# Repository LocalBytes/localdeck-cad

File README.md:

# LocalDeck CAD

## About

This is the repo for the LocalDeck CAD; it is split into multiple parts:

- [freecad](./freecad)
    - Uses FreeCAD v1
    - Contains all of the mechanical CAD resources
    - You should start with [asm-localdeck](./freecad/asm-localdeck.FCStd)
- [kicad](./kicad)
    - Uses Kicad v8
    - Contains all of the electrical CAD resources

## Contributing

The best way to contribute to the LocalDeck (and it's configurator) is by using the development version in your HomeAssistant, and reporting any issues you find.
Additionally, we would appreciate it if you were to be active on the Forum should we solicit feedback on a new feature or change.

We do not recommend pull-requests to this repo. Git doesn't handle CAD files too well.
If you are a mechanical or electrical engineer, the best way to contribute would be by opening 
If you are a developer, you can also contribute by submitting a pull request to this repository. Please be aware that any code contributed will become the property of Allport-IT LTD.

## Licence
This project is currently published with no specific licence:
- This program is distributed in the hope that it will be useful,
  but WITHOUT ANY WARRANTY
- As an individual user, you are free learn from it, and use it in your own projects
- You must not claim it as your own

Unless otherwise stated, all code is &copy; Allport-IT LTD. All rights reserved.  
"LocalBytes" and the LocalBytes Logo are &reg; of Allport-IT LTD.

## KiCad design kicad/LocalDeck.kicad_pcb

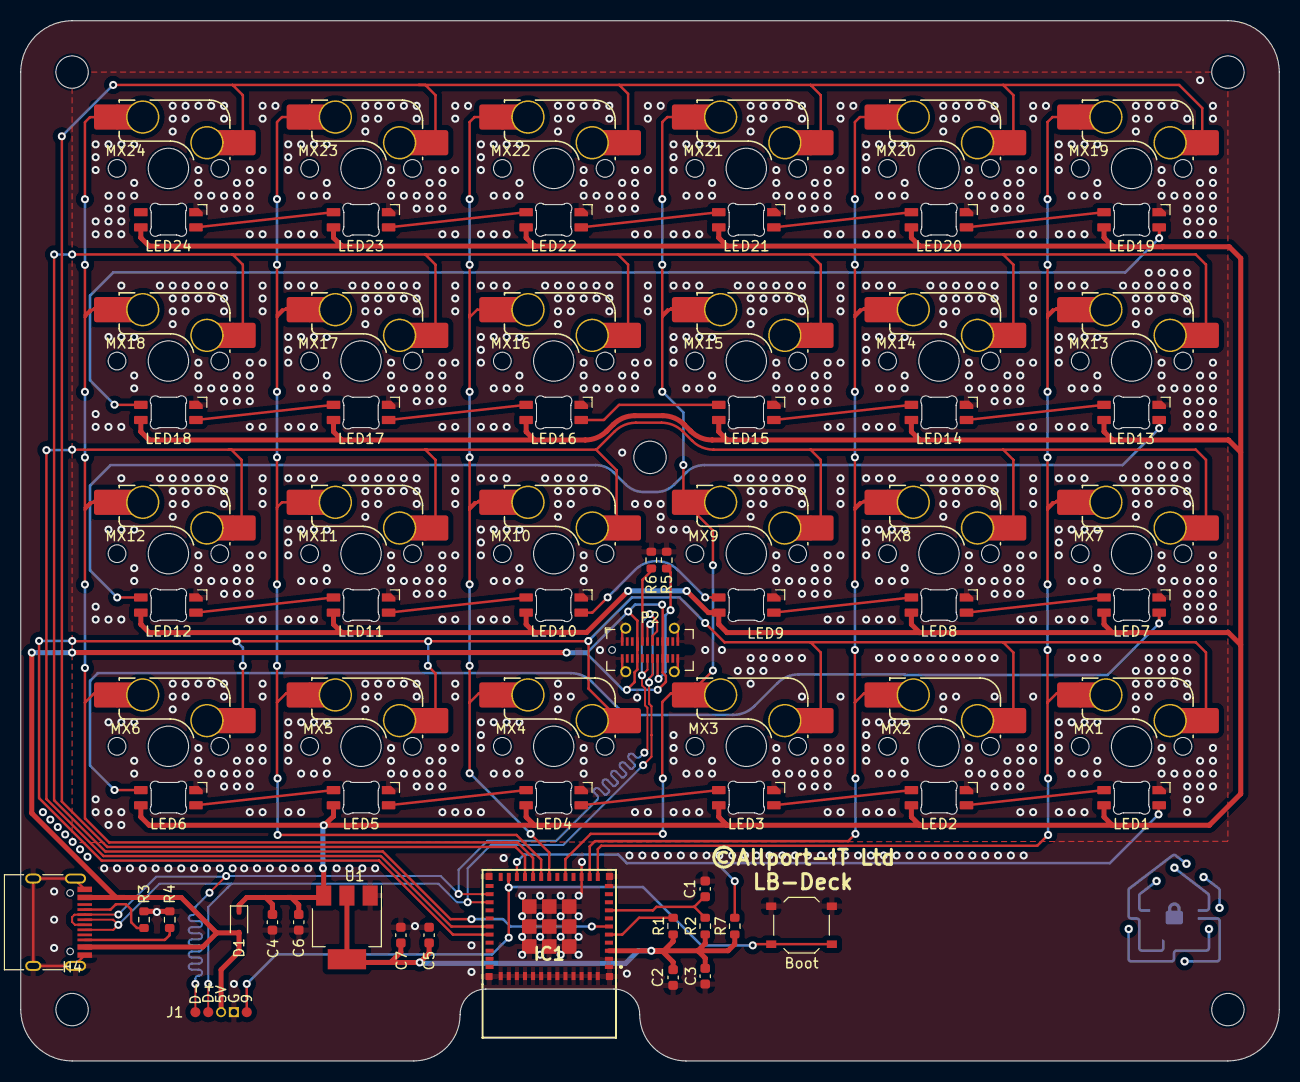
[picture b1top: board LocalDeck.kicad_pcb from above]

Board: 2 copper layers, 124.5 x 102.9 mm, 74 parts (0 on the bottom side), 47 nets.

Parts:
C1: 1uf; C_0603_1608Metric
C2, C4: 10uf; C_0603_1608Metric
C3, C6, C7: 0.1uf; C_0603_1608Metric
C5: 22uf; C_0603_1608Metric
D1: BAT60A; D_SOD-323
H1, H2, H3, H4, H5: MountingHole; MountingHole_3.2mm_M3
IC1: ESP32-C3-MINI-1-N4; ESP32C3MINI1N4
J1: Conn_Prog; ProgrammingHeader
LED1, LED2, LED3, LED4, LED5, LED6, LED7, LED8, LED9, LED10, LED11, LED12, LED13, LED14, LED15, LED16, LED17, LED18, LED19, LED20, LED21, LED22, LED23, LED24: MX_SK6812MINI-E; LED_MX_6028R-ROT
MX1, MX2, MX3, MX4, MX5, MX6, MX7, MX8, MX9, MX10, MX11, MX12, MX13, MX14, MX15, MX16, MX17, MX18, MX19, MX20, MX21, MX22, MX23, MX24: MX_SW_HS; SW_MX_HS_1u
P1: USB_C_Receptacle_USB2.0; USB_C_Receptacle_HRO_TYPE-C-31-M-12
P2: USB_C_Receptacle_USB2.0; USB_C_Receptacle_GCT_USB4115-03-C
R1, R2, R7: 10k; R_0603_1608Metric
R3, R4, R5, R6: 5k; R_0603_1608Metric
SW1: Boot; SW_Push_1P1T_XKB_TS-1187A
U1: AMS1117-3.3; SOT-223-3_TabPin2

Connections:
+3.3V: C2.2, C3.2, C5.1, C7.1, IC1.3 (3V3), R1.1, R2.1, R7.2, U1.2 (VO)
+5V: C4.1, C6.1, D1.1 (K), LED1.1 (VDD), LED2.1 (VDD), LED3.1 (VDD), LED4.1 (VDD), LED5.1 (VDD), LED6.1 (VDD), LED7.1 (VDD), LED8.1 (VDD), LED9.1 (VDD), LED10.1 (VDD), LED11.1 (VDD), LED12.1 (VDD), LED13.1 (VDD), LED14.1 (VDD), LED15.1 (VDD), LED16.1 (VDD), LED17.1 (VDD), LED18.1 (VDD), LED19.1 (VDD), LED20.1 (VDD), LED21.1 (VDD), LED22.1 (VDD), LED23.1 (VDD), LED24.1 (VDD), U1.3 (VI)
/USB_D+: IC1.27 (IO19), J1.4, P1.A6 (D+), P1.B6 (D+), P2.A6 (D+), P2.B6 (D+)
/USB_D-: IC1.26 (IO18), J1.5, P1.A7 (D-), P1.B7 (D-), P2.A7 (D-), P2.B7 (D-)
/col0: IC1.12 (IO0), MX1.2, MX7.2, MX13.2, MX19.2
/col1: IC1.13 (IO1), MX2.2, MX8.2, MX14.2, MX20.2
/col2: IC1.16 (IO10), MX3.2, MX9.2, MX15.2, MX21.2
/col3: IC1.18 (IO4), MX4.2, MX10.2, MX16.2, MX22.2
/col4: IC1.19 (IO5), MX5.2, MX11.2, MX17.2, MX23.2
/col5: IC1.20 (IO6), MX6.2, MX12.2, MX18.2, MX24.2
/esp_boot: IC1.23 (IO9), J1.1, SW1.2
/esp_en: C1.1, IC1.8 (EN), R2.2
/led: IC1.22 (IO8), LED1.3 (DIN), R7.1
/row0: IC1.31 (TXD0), MX1.1, MX2.1, MX3.1, MX4.1, MX5.1, MX6.1
/row1: IC1.30 (RXD0), MX7.1, MX8.1, MX9.1, MX10.1, MX11.1, MX12.1
/row2: IC1.6 (IO3), MX13.1, MX14.1, MX15.1, MX16.1, MX17.1, MX18.1
/row3: IC1.21 (IO7), MX19.1, MX20.1, MX21.1, MX22.1, MX23.1, MX24.1
GND: C1.2, C2.1, C3.1, C4.2, C5.2, C6.2, C7.2, IC1.1 (GND_1), IC1.2 (GND_2), IC1.11 (GND_3), IC1.14 (GND_4), IC1.36 (GND_5), IC1.37 (GND_6), IC1.38 (GND_7), IC1.39 (GND_8), IC1.40 (GND_9), IC1.41 (GND_10), IC1.42 (GND_11), IC1.43 (GND_12), IC1.44 (GND_13), IC1.45 (GND_14), IC1.46 (GND_15), IC1.47 (GND_16), IC1.48 (GND_17), IC1.49 (GND_18), IC1.50 (GND_19), IC1.51 (GND_20), IC1.52 (GND_21), IC1.53 (GND_22), IC1.54 (GND_23), IC1.55 (GND_24), IC1.56 (GND_25), IC1.57 (GND_26), IC1.58 (GND_27), IC1.59 (GND_28), IC1.60 (GND_29), IC1.61 (GND_30), J1.2, LED1.4 (VSS), LED2.4 (VSS), LED3.4 (VSS), LED4.4 (VSS), LED5.4 (VSS), LED6.4 (VSS), LED7.4 (VSS), LED8.4 (VSS), LED9.4 (VSS), LED10.4 (VSS), LED11.4 (VSS), LED12.4 (VSS), LED13.4 (VSS), LED14.4 (VSS), LED15.4 (VSS), LED16.4 (VSS), LED17.4 (VSS), LED18.4 (VSS), LED19.4 (VSS), LED20.4 (VSS), LED21.4 (VSS), LED22.4 (VSS), LED23.4 (VSS), LED24.4 (VSS), P1.A1 (GND), P1.A12 (GND), P1.S1 (SHIELD), P2.A1 (GND), P2.A12 (GND), P2.B1 (GND), P2.B12 (GND), P2.S1 (SHIELD), R3.1, R4.1, R5.1, R6.1, SW1.1, U1.1 (GND)
unnamed: IC1.5 (IO2), R1.2
unnamed: LED1.2 (DOUT), LED2.3 (DIN)
unnamed: LED2.2 (DOUT), LED3.3 (DIN)
unnamed: LED3.2 (DOUT), LED4.3 (DIN)
unnamed: LED4.2 (DOUT), LED5.3 (DIN)
unnamed: LED5.2 (DOUT), LED6.3 (DIN)
unnamed: LED6.2 (DOUT), LED7.3 (DIN)
unnamed: LED7.2 (DOUT), LED8.3 (DIN)
unnamed: LED8.2 (DOUT), LED9.3 (DIN)
unnamed: LED9.2 (DOUT), LED10.3 (DIN)
unnamed: LED10.2 (DOUT), LED11.3 (DIN)
unnamed: LED11.2 (DOUT), LED12.3 (DIN)
unnamed: LED12.2 (DOUT), LED13.3 (DIN)
unnamed: LED13.2 (DOUT), LED14.3 (DIN)
unnamed: LED14.2 (DOUT), LED15.3 (DIN)
unnamed: LED15.2 (DOUT), LED16.3 (DIN)
unnamed: LED16.2 (DOUT), LED17.3 (DIN)
unnamed: LED17.2 (DOUT), LED18.3 (DIN)
unnamed: LED18.2 (DOUT), LED19.3 (DIN)
unnamed: LED19.2 (DOUT), LED20.3 (DIN)
unnamed: LED20.2 (DOUT), LED21.3 (DIN)
unnamed: LED21.2 (DOUT), LED22.3 (DIN)
unnamed: LED22.2 (DOUT), LED23.3 (DIN)
unnamed: LED23.2 (DOUT), LED24.3 (DIN)
unnamed: P1.A5 (CC1), R3.2
unnamed: P1.B5 (CC2), R4.2
unnamed: P2.A5 (CC1), R6.2
unnamed: P2.B5 (CC2), R5.2
VBUS: D1.2 (A), J1.3, P1.A4 (VBUS), P1.A9 (VBUS), P2.A4 (VBUS), P2.A9 (VBUS), P2.B4 (VBUS), P2.B9 (VBUS)

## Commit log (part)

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2024-07-26 Inital Commit
2024-07-26 Inital Commit - Adding everything
2024-07-26 fix: :shushing_face:
2024-07-30 feat: Added programming Header
2024-07-31 chore: Removed unused part
2024-07-31 feat: Made enclosure compatable with new feet
2024-07-31 feat: Updated asm-enclosure to show new feet
2024-08-02 chore: Added exports to ignore
2024-08-02 feat(freecad): Increased snap-fit thickness
2024-08-07 feat(freecad): Added usb-c part for clearance
2024-08-07 refactor(freecad): Moved `part-cap` to `part-key-cap`
2024-08-07 feat(freecad): Moved asm-key to Ondsel Assembly
2024-08-07 feat(freecad): Rebuilt main assembly
2024-08-07 fix: Unlocks all
2024-08-07 fix: Added more USB Clearance
2024-08-14 feat(freecad): Added boot hole & stats window
2024-08-14 chore(kicad): Added measurements & part numbers
2024-08-14 chore: Removed text mode from FCStd
2024-08-18 chore: Latest FCad version, previous didn't calculate suptractive patterns properly!
2024-12-22 chore: FreeCAD 1.0.0
